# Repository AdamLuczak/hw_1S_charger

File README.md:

# Single-Cell 1S Charger Project

## Overview
This repository contains the design files for a simple and versatile single-cell 1S charger module. This charger is designed as an independent module with a battery holder, making it a plug-and-play solution for charging applications. It features a USB socket for power input and additional footprints for alternative connectors like JST, offering flexibility in power connection options.

The charger is based on the MCP73832, a highly integrated linear charge management controller suitable for use within a wide range of battery sizes and chemistries. Its compact form factor and simple functionality make it an ideal choice for portable applications.

## Features of MCP73832
- Linear charge management controller optimized for single-cell lithium-ion and lithium-polymer batteries.
- Programmable charge current from 15 mA to 500 mA.
- Preconditioning of deeply discharged batteries.
- Automatic end-of-charge control via charge termination and auto-recharge.
- Charge status output pin that can drive an LED.
- Thermal regulation to maximize charge rate without risk of overheating.

## Schematic
The schematic details the electrical design, showing how the MCP73832 is integrated to provide safe and efficient charging.

## PCB Layout
The PCB layout illustrates the component placement and routing, designed to be compact and efficient.

## Usage
To use the charger, connect a single-cell 1S battery to the battery holder, and power the charger via the USB socket or alternative power connector. An LED indicator provides real-time charging status based on the output from the MCP73832.

## Notes
- Make sure to use the charger with the appropriate battery chemistry and specifications as intended by the design.
- The charger design is based on the MCP73832 charge management controller which is optimized for single-cell lithium-ion and lithium-polymer batteries.
- It is important to verify the power input source and ensure that the USB power supply complies with the required specifications for charging.

## Contributions and Feedback
Contributions to this project are welcome. If you have suggestions for improvement or have developed additional features, please fork the repository, make your changes, and submit a pull request. For any questions or issues, please open an issue in the GitHub repository.

## License
This charger project is licensed under the MIT License with the following terms:

- **Permission to Use**: You are free to use, modify, and distribute this charger design in both private and commercial settings.
- **Attribution Requirement**: While not required, attribution to the original author, Adam Łuczak, is appreciated. This can be done through a citation or a link back to this repository.
- **No Warranty**: This design is provided "as is", without warranty of any kind. Use it at your own risk.
- **Liability**: The author is not liable for any damages or losses that may arise from the use of this design.

For the full terms and conditions, please refer to the MIT License documentation.

## Contact
Should you have any inquiries or suggestions regarding this charger project, please don't hesitate to contact Adam Łuczak at adam.luczak@outlook.com.

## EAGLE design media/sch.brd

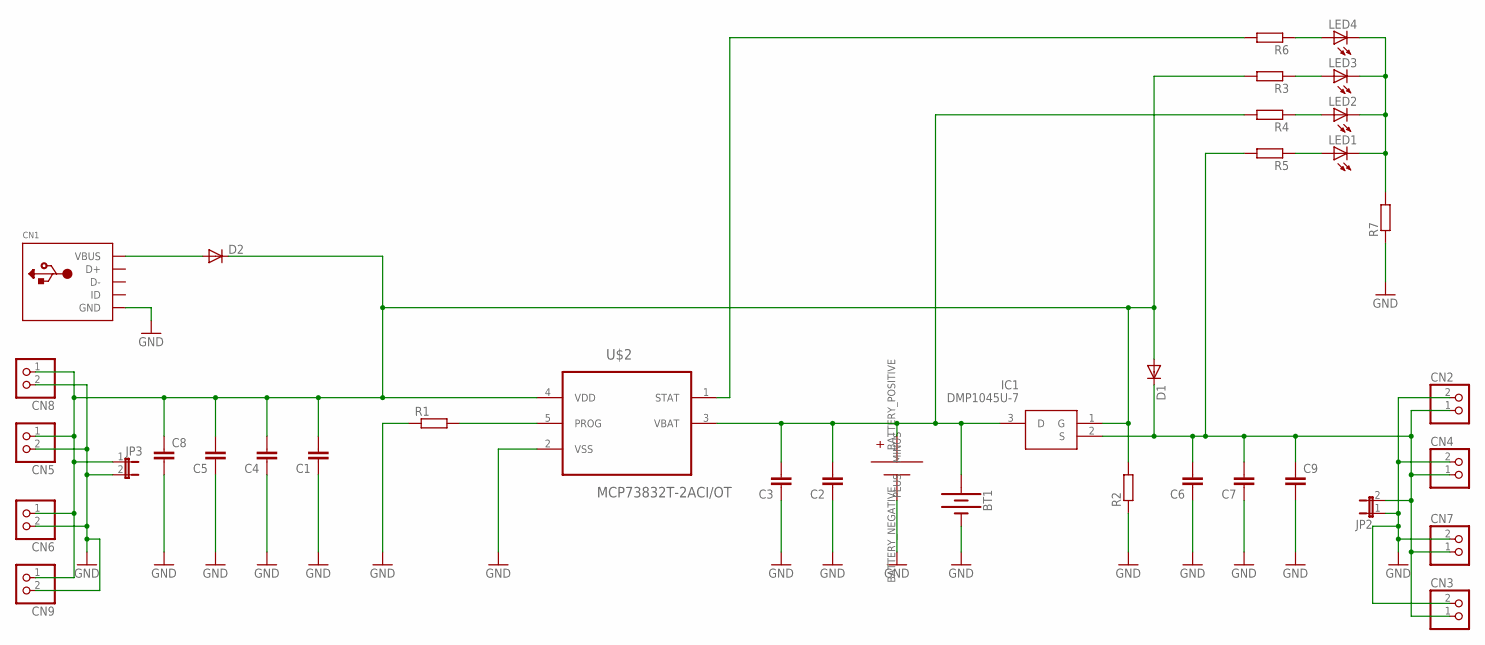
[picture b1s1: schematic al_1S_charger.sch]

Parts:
BT1: BATTERY-18650; BATTERY_18650-HOLDER
C1, C2, C3, C4, C5, C6, C7: C-EUC0603; C0603
C8, C9: C-EUC1210; C1210
CN1: USBMINIB; USB-MINIB
CN2, CN3, CN8, CN9: JST_2PIN-SMT-RA; JST-PH-2-SMT-RA
CN4, CN5, CN6, CN7: JST_2PIN-THM-RA; JST-PH-2-THM-RA
D1, D2: DIODE-SMB; SMB
IC1: DMP1045U-7; SOT96P240X100-3N
JP2, JP3: JP1E; JP1
LED1, LED2, LED3, LED4: LEDCHIP-LED0603; CHIP-LED0603
R1, R2, R3, R4, R5, R6, R7: R-EU_R0603; R0603
U$1: SMT18650_SMT18650; SMT18650_18650SMT
U$2: MCP73832T-2ACI/OT; SOT95P280X145-5N

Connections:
GND: BT1.GND@1 (-), C1.1, C2.1, C3.1, C4.1, C5.1, C6.1, C7.1, C8.2, C9.2, CN1.GND, CN2.2 (1), CN3.2 (1), CN4.2 (1), CN5.2 (1), CN6.2 (1), CN7.2 (1), CN8.2 (1), CN9.2 (1), JP2.1, JP3.2, R1.1, R2.1, R7.1, U$1.BATTERY_NEGATIVE (MINUS), U$2.2 (VSS)
unnamed: BT1.PWR@1 (+), C2.2, C3.2, IC1.3 (D), R4.2, U$1.BATTERY_POSITIVE (PLUS), U$2.3 (VBAT)
unnamed: LED4.A, R6.1
unnamed: C1.2, C4.2, C5.2, C8.1, CN5.1 (2), CN6.1 (2), CN8.1 (2), CN9.1 (2), D1.A, D2.C, IC1.1 (G), JP3.1, R2.2, R3.2, U$2.4 (VDD)
unnamed: CN1.VBUS, D2.A
unnamed: R1.2, U$2.5 (PROG)
unnamed: LED3.A, R3.1
unnamed: LED2.A, R4.1
unnamed: LED1.A, R5.1
unnamed: C6.2, C7.2, C9.1, CN2.1 (2), CN3.1 (2), CN4.1 (2), CN7.1 (2), D1.C, IC1.2 (S), JP2.2, R5.2
unnamed: R6.2, U$2.1 (STAT)
unnamed: LED1.C, LED2.C, LED3.C, LED4.C, R7.2

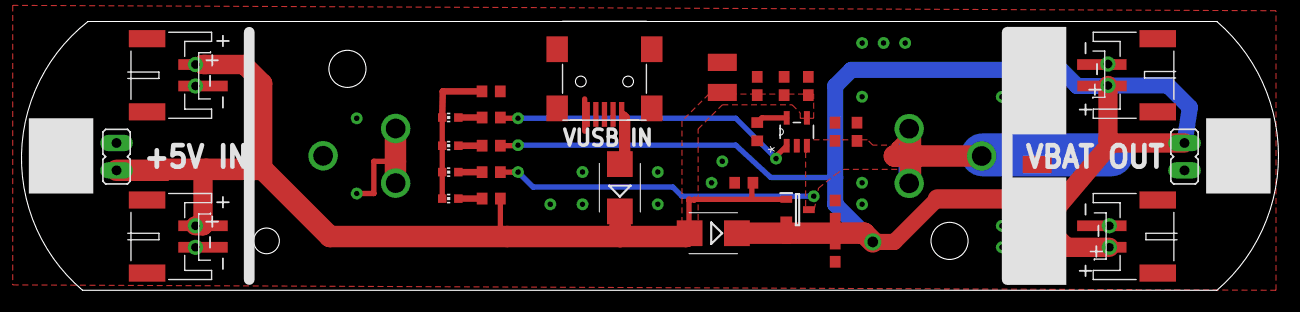
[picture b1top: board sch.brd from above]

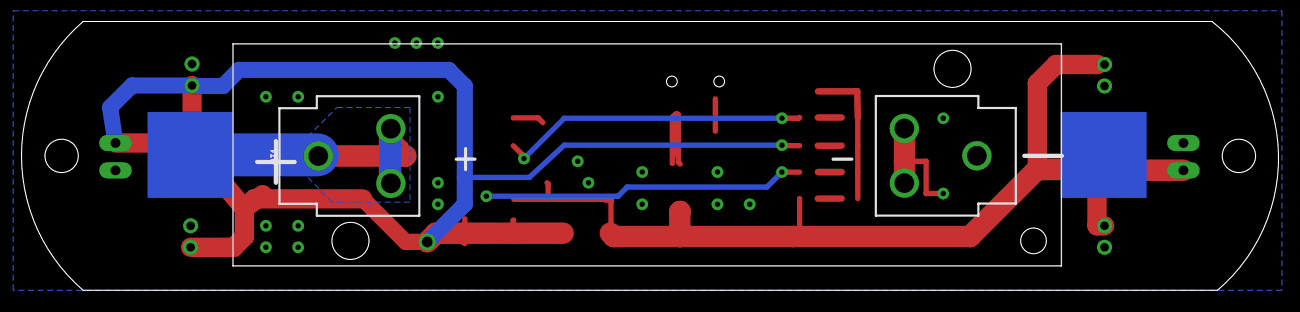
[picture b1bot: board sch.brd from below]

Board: 2 copper layers, 116.9 x 25.0 mm, 37 parts (2 on the bottom side), 12 nets.

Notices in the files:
README.md:
License: MIT
parts and their libraries:
SparkFun-Batteries: Licensing: Creative Commons ShareAlike 4.0 International - https://creativecommons.org/licenses/by-sa/4.0
